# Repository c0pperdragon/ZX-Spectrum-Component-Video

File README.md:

# ZX-Spectrum-Component-Video
Component video (YPbPr) output for the ZX Spectrum computer 

## General

The ZX Spectrum in its original form produces a radio frequency signal that can be fed into an analog TV. The quality of this
signal is very poor, but this can be improved by a simple modification that will make the ZX Spectrum output a composite video
signal instead. While this is actually better, it is nowhere near good. To bring the video quality to the next level,
this modification will produce a component video signal (YPbPr) that should be as good as an analog signal can possible get.
This video signal can be used either directly with a TV that has a YPbPr input, or it can be passed through a dedicated upscaler device
("Framemeister", "OSSC", etc.) before displaying on an HDMI screen.

This hardware modification is a more compact version of the solution that uses an A-Video board with seperate level shifters.
It tries to solve various shortcomings of https://github.com/c0pperdragon/A-VideoBoard/tree/master/zxspectrummod :

- Smaller and cheaper to make
- No need to modify the case of the ZX Spectrum
- No need to remove any components besides the RF modulator.

## Theory of operation

The mod board passively listens to various digital data lines through which the ULA communicates with the rest of the 
main board - specifically the signals CAS,RW,IOREQ and the data bus. This information is processed by the FPGA 
to figure out what image the ULA intends to display. The FPGA drives a simple 3-channel digital-to-analog converter built from
resistors to produce the 3 output voltages of the YPbPr signal.
Because the main board runs with 5 volt logic levels and the FPGA can only work with 3.3 volts, a voltage regulator and
two input level shifter ICs are necessary (on the bottom side of the mod board). 

## Video output possibilities

- 288p (default) or 576p
- YPbPr (default) or RGsB

Output modes can be selected by jumpers or optional switches.

The color palette I am using has slightly softened colors. The original monochromatic colors are just too hard on
my eyes especially when viewed on a modern display.
I took the platte from [https://lospec.com/palette-list/zx-spectrum] and in my opinion this really looks great.

## Drawbacks

Installation of the mod requires complete removal of the RF modulator. This also implies that an
existing composite video mod will no longer be available. Without further modification the 
ZX Spectrum will then work with component video output exclusively.

If you need composite video additionally you can wire up an extra connector, as the
original analog signals are still being produced by the video output circuit.

## Images

## Configuration jumpers

You can switch to 576p (enhanced definition TV - double vertical resolution) by bridging the jumper J10.
Likewise you can switch to RGsB output by briding the jumper J3.
Both can either be done with a jumper (permenant setting) or an optional external switch. You can
do that in whatever way you like - maybe there is even a solution that does not require to modify the
case.

## Video adapter cable

The mod uses a small TRRS jack to provide the component video signal. For use with standard cabling,
you will need an adapter to break out the 3 lines to individual RCA jacks. Take care to use a cable
that has the common ground on the sleeve of the tip-ring-ring-sleeve plug.
One possible ready-made product would be: [https://www.delock.de/produkte/S_62499/merkmale.html]

## Installation details

Remove an existing RF modulator completely and remove all the solder from the mounting holes.
Put the mod boad in place of the modulator and solder the two mounting pins. These pins will also
connect the GND levels.
For the following cabling I recommend some single stranded wire that is just thin enough to fit
into the various via holes of the main board. Using via holes wherever possible is the least invasive
option and is also easily reversible.

### Power

+5V power supply must be wired to the JPOWER1 hole of the board. A usable voltage source can be found
for example near the headphone jacks. Do not use the power line that was originally driving the 
RF modulator, as this is comming through some resistor and will not deliver enough current.

### Control signals

The three control signals CAS, IOREQ, WR can best be taken from the backside of the main board directly from
the ULA socket pins (see pin_assignment.txt for more details).

### Data signals

Signals D0 to D7 can be taken from various vias through which the data signals are 
sent on their way between the ULA and the RAM chips. 
The exact locations may differ with board revision. You may have to probe around with a multimeter
to find a conveniently located via for each signal. In the case that you can not 
find any accessible via, you can also solder your wire directly to the RAM chip (but only as last ressort).  

## Assembled boards

I have provided all my assembled boards to videogameperfection.com for sale. 
Please have a look at their website first, and if everything is out of stock, you
can try to contact me directly at at reinhard.grafl (at) aon.at.

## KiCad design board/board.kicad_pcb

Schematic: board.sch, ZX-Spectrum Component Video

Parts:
C1, C2, C3, C4, C5: 10uF; C_0805_2012Metric_Pad1.15x1.40mm_HandSolder
C6, C7, C8, C9, C11, C12, C13, C14, C15, C16, C17, C18, C19, C20, C21, C22, C23, C24, C25, C31, C32, C33, C34: 100nF; C_0603_1608Metric_Pad1.05x0.95mm_HandSolder
IC1, IC2: LVC245A; SSOP-20_5.3x7.2mm_P0.65mm
J1: Conn_01x06_Male; PinHeader_1x06_P2.54mm_Vertical
J2: AudioJack4_Ground; Conrad 4pin audio jack
J3, J10: Conn_01x02; PinHeader_2x01_P2.54mm_Vertical
J5, J6, J7, J8, J9: Conn_01x01_Male; PinHeader_1x01_P2.54mm_Vertical
J11: Conn_01x05_Male; PinHeader_1x05_P2.54mm_Vertical
JPOWER1: Conn_01x01_Male; PinHeader_1x01_P2.54mm_Vertical
JTAG1: CONN_02X05; PinHeader_2x05_P2.54mm_Vertical
L1, L2, L3: 10uH; C_0805_2012Metric_Pad1.15x1.40mm_HandSolder
OSC1: LFSPXO024957; Oscillator_SMD_EuroQuartz_XO53-4Pin_5.0x3.2mm_HandSoldering
R1: 1k1; R_0805_2012Metric_Pad1.15x1.40mm_HandSolder
R2, R7, R12: 1k; R_0805_2012Metric_Pad1.15x1.40mm_HandSolder
R3, R8, R13: 2k; R_0805_2012Metric_Pad1.15x1.40mm_HandSolder
R4, R9, R14: 4k; R_0805_2012Metric_Pad1.15x1.40mm_HandSolder
R5, R10, R15: 8k; R_0805_2012Metric_Pad1.15x1.40mm_HandSolder
R6, R11, R16: 16k; R_0805_2012Metric_Pad1.15x1.40mm_HandSolder
R17, R18, R19: 150; R_0805_2012Metric_Pad1.15x1.40mm_HandSolder
R20, R21, R22, R23, R24, R25, R26: 10k; R_0805_2012Metric_Pad1.15x1.40mm_HandSolder
R27, R28, R29: 75; R_0805_2012Metric_Pad1.15x1.40mm_HandSolder
REG1: LM1117IMPX-3.3; SOT-223
U1: THS7316; SOIC-8_3.9x4.9mm_P1.27mm
U2: 10M02SCE144; QFP_144_GND

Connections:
+5V: C1.1, JPOWER1.1, REG1.3
/3V3A: C2.1, C6.1, C8.1, C9.2, IC1.1, IC1.20, IC2.1, IC2.20, JTAG1.4, L1.2, L2.2, L3.2, OSC1.1, OSC1.4, R20.2, R21.2, R22.2, REG1.2, REG1.4
/3V3B: C4.1, C11.1, C12.1, C13.1, C14.1, C15.1, C16.1, C17.1, C18.1, C19.1, C20.1, C21.1, C22.1, C23.1, C24.1, C25.1, L1.1, R24.1, R25.1, U2.1, U2.12, U2.22, U2.29, U2.36, U2.37, U2.43, U2.56, U2.58, U2.64, U2.72, U2.73, U2.82, U2.93, U2.102, U2.108, U2.109, U2.111, U2.113, U2.115, U2.118, U2.121, U2.122, U2.132, U2.136, U2.142, U2.144
/3V3C: C3.1, C31.1, C32.1, C33.1, C34.1, L2.1, U2.2, U2.34, U2.35, U2.71, U2.107
/3V3D: C5.1, C7.2, L3.1, U1.4
/CAS: IC1.6, J1.4
/CAS_3V: IC1.14, U2.139
/D0: IC1.8, J1.3
/D0_3V: IC1.12, U2.138
/D1: IC1.9, J1.2
/D1_3V: IC1.11, U2.137
/D2: IC2.2, J1.1
/D2_3V: IC2.18, U2.124
/D3: IC2.3, J11.5
/D3_3V: IC2.17, U2.123
/D4: IC2.4, J11.4
/D4_3V: IC2.16, U2.117
/D5: IC2.6, J11.3
/D5_3V: IC2.14, U2.116
/D6: IC2.8, J11.2
/D6_3V: IC2.12, U2.114
/D7: IC2.9, J11.1
/D7_3V: IC2.11, U2.112
/IOREQ: IC1.4, J1.5
/IOREQ_3V: IC1.16, U2.140
/LINEDOUBLE: J10.2, U2.31
/PB: J2.R1, R28.1
/PB2: R28.2, U1.7
/PR: J2.R2, R27.1
/PR2: R27.2, U1.8
/RGBMODE: J3.2, U2.32
/WR: IC1.2, J1.6
/WR_3V: IC1.18, U2.141
/Y: J2.T, R29.1
/Y2: R29.2, U1.6
GND: C1.2, C2.2, C3.2, C4.2, C5.2, C6.2, C7.1, C8.2, C9.1, C11.2, C12.2, C13.2, C14.2, C15.2, C16.2, C17.2, C18.2, C19.2, C20.2, C21.2, C22.2, C23.2, C24.2, C25.2, C31.2, C32.2, C33.2, C34.2, IC1.3, IC1.5, IC1.7, IC1.10, IC1.19, IC2.5, IC2.7, IC2.10, IC2.19, J2.S, J3.1, J5.1, J6.1, J7.1, J8.1, J9.1, J10.1, JTAG1.2, JTAG1.10, OSC1.2, R17.2, R18.2, R19.2, R23.1, R26.1, REG1.1, U1.5, U2.11, U2.20, U2.30, U2.38, U2.45, U2.57, U2.66, U2.83, U2.96, U2.104, U2.110, U2.119, U2.133, U2.143, U2.145
unnamed: JTAG1.1, R23.2, U2.16
unnamed: JTAG1.3, U2.18
unnamed: JTAG1.5, R20.1, U2.15
unnamed: JTAG1.9, R21.1, U2.17
unnamed: OSC1.3, U2.25
unnamed: R1.1, U2.46
unnamed: R1.2, R2.2, R3.2, R4.2, R5.2, R6.2, R17.1, U1.3
unnamed: R2.1, U2.47
unnamed: R3.1, U2.48
unnamed: R4.1, U2.49
unnamed: R5.1, U2.50
unnamed: R6.1, U2.51
unnamed: R7.1, U2.52
unnamed: R8.1, U2.53
unnamed: R9.1, U2.59
unnamed: R10.1, U2.60
unnamed: R7.2, R8.2, R9.2, R10.2, R11.2, R18.1, U1.2
unnamed: R11.1, U2.61
unnamed: R12.1, U2.63
unnamed: R12.2, R13.2, R14.2, R15.2, R16.2, R19.1, U1.1
unnamed: R13.1, U2.65
unnamed: R14.1, U2.67
unnamed: R15.1, U2.69
unnamed: R16.1, U2.70
unnamed: R22.1, U2.13
unnamed: R24.2, U2.135
unnamed: R25.2, U2.131
unnamed: R26.2, U2.120

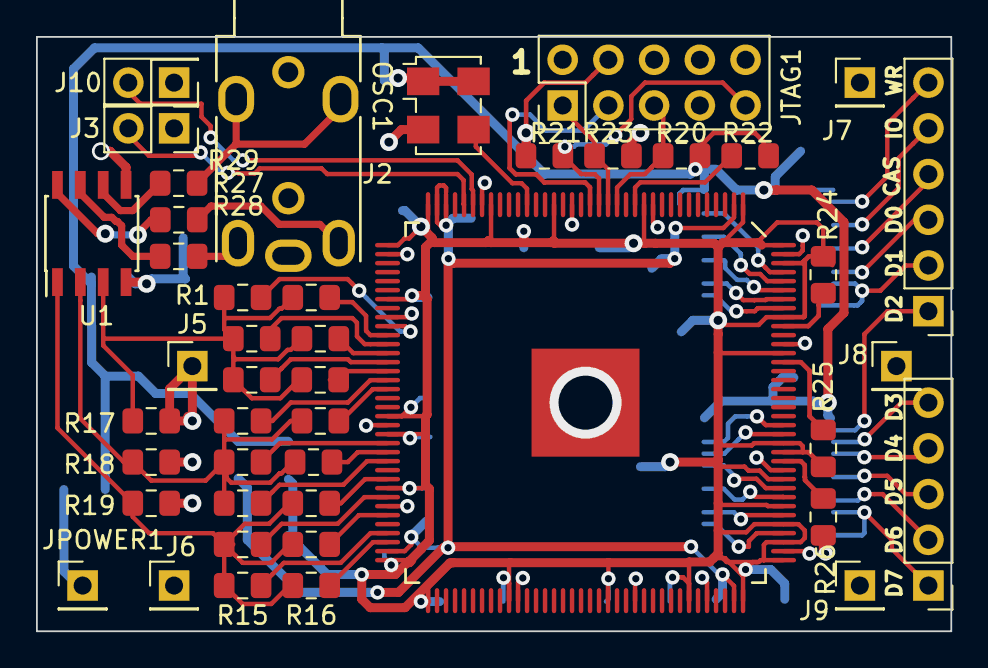
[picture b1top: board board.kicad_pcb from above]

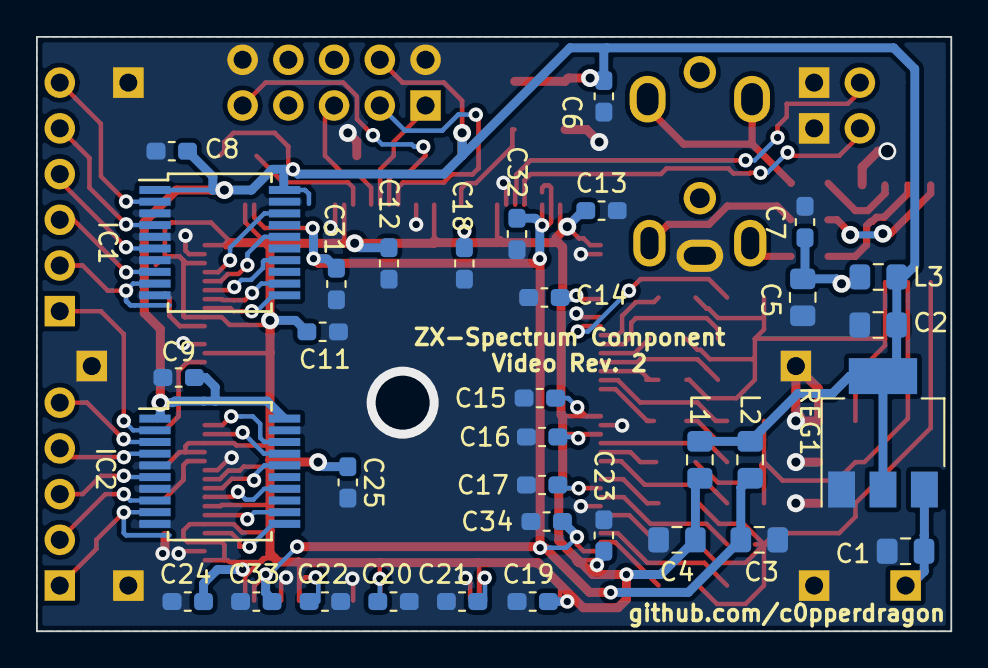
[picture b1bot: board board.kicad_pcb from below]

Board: 2 copper layers, 50.8 x 33.0 mm, 78 parts (34 on the bottom side), 64 nets.

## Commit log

2020-02-29 Start layouting
2020-03-02 Ongoing design
    Squeezing all necessary electronics onto a 3.3mm x 5.1mm board
2020-03-03 Layout complete (version 1)
2020-04-28 Pin assignment list
2020-05-02 Start development of specific firmware version.
2020-05-03 Firmware fixes and documentation
2020-05-03 Docu
2020-05-03 More docu
2020-05-03 Typo
2020-05-16 Redesign mode jumpers. Minor fixes in silk screen.
2020-05-17 More documentation
2020-05-19 Prepare project for test image generator.
2020-05-19 Image data
2020-05-20 Working test program
2020-05-21 Modify PCB for easier assembly
2020-05-22 Simplified border color generation. Fix up test program.
2020-07-02 Upload image
2021-01-27 Add BOM
2022-04-28 Increase border size and tweak sync pulses.
2023-10-15 Generate auxilary 14MHz clock in case it is needed by a faulty ULA
